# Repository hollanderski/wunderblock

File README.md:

# Wunderblock
webGL interface for "Wunderblock", art installation exhibited at PHITECO 2022

<br>

Created by Ninon Lizé Masclef and Syd Reynal, the installation Wunderblock proposes a reflection on telepresence and the ambivalence it carries through the oppositions presence-absence, virtual-embodied, simultaneity-latency. Wunderblock mediates the touch, through a tension between organic traces embedded in the material of a tactile sensor and digital traces reincarnated in the flesh of the virtual world.
As it breaks the simultaneity traditionally at work in the real-time human-machine interface, Wunderblock opens up power of the après-coup. From traces on the walls of Lascaux to the prophylaxis of the Metaverse, this work thus questions the multiplicity of modes of collective presence and forms of memories that materialize there.

The installation was exhibited during the seminar PHITECO (Philosophy Technology Cognition) 2022 at University of Technology of Compiègne whose theme was : "Technical mediation of presence". Read the <a href="http://ninonlm.com/hyperobjects/wunderblock/program.pdf">full program</a> of the seminar. 

<br>

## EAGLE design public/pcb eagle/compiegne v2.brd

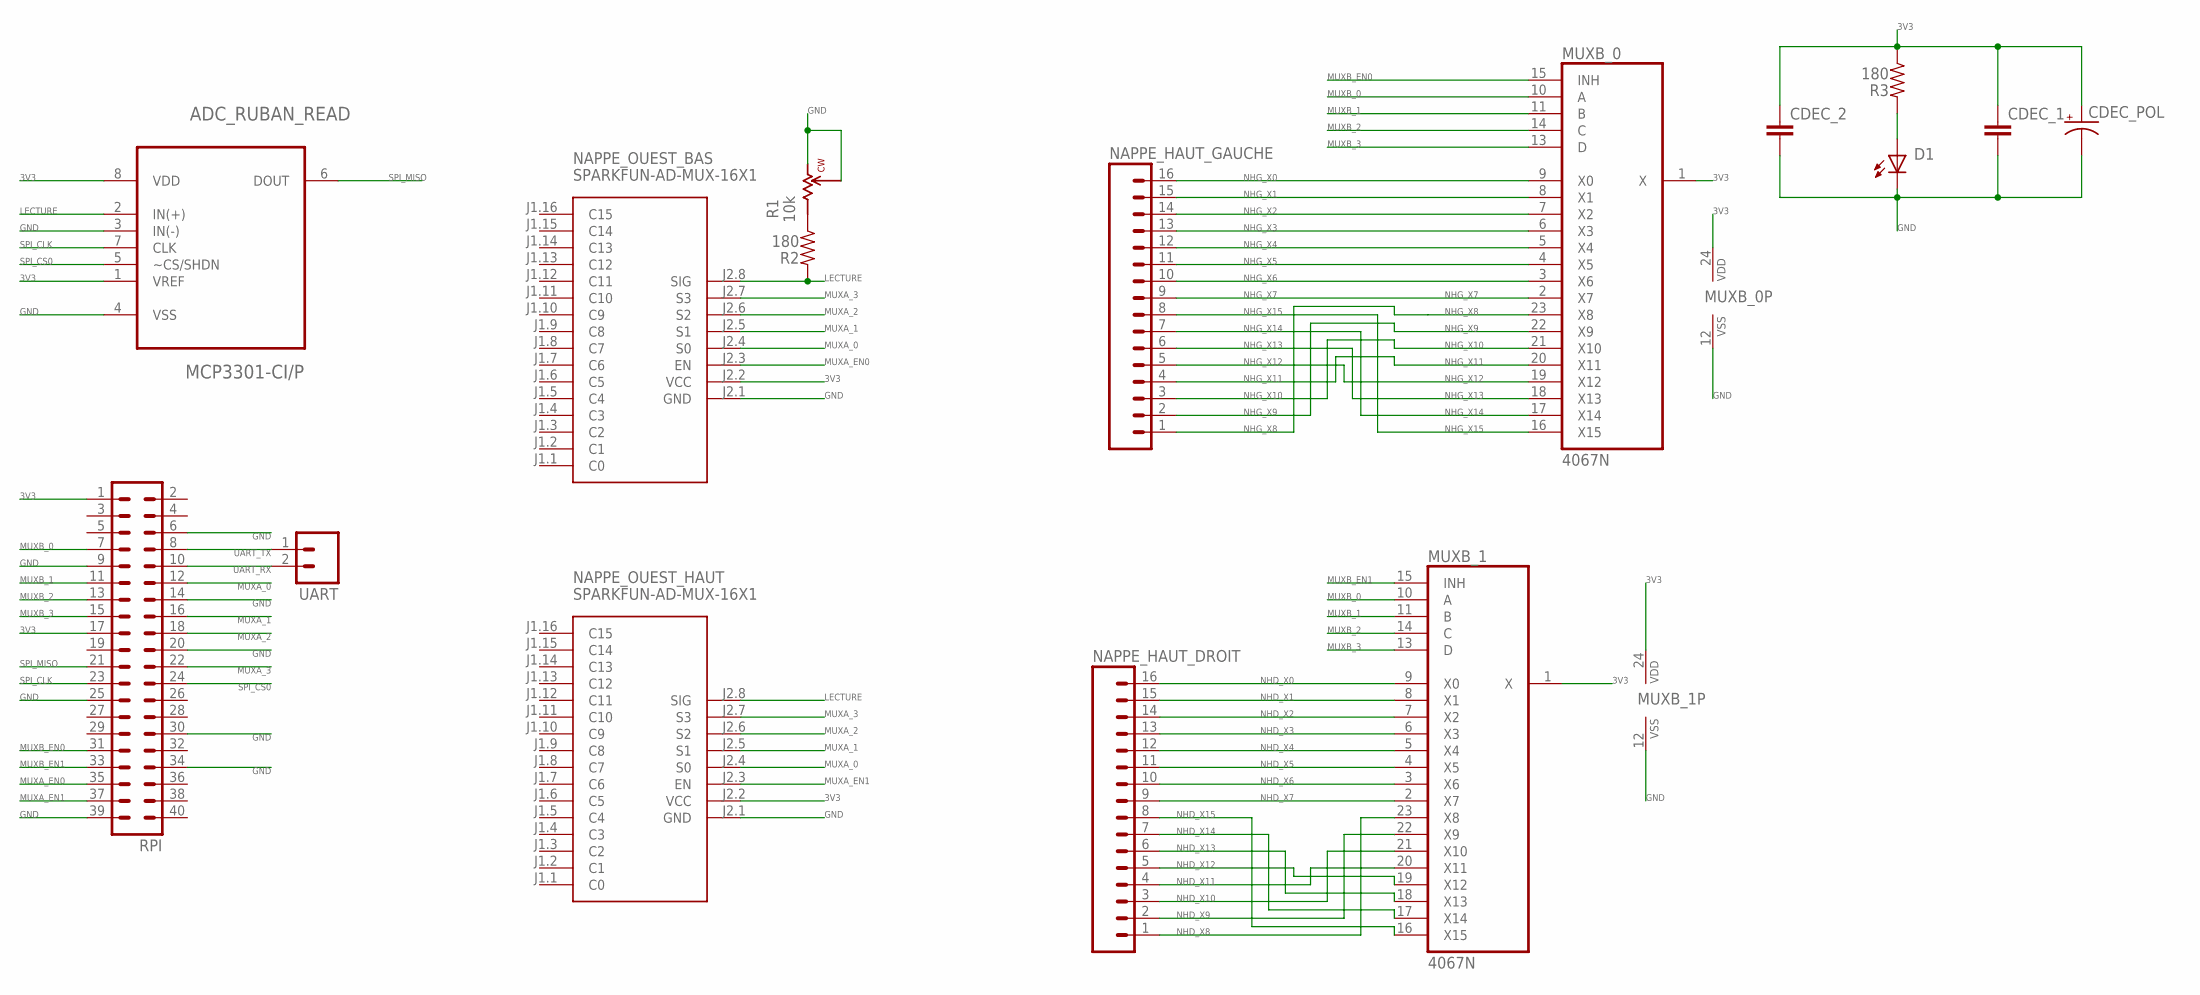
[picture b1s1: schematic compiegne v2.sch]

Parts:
ADC_RUBAN_READ: MCP3301-CI/P; DIP254P762X432-8
CDEC_1, CDEC_2: PASSIF-CAP-PTH; CAP-PTH
CDEC_POL: PASSIF-CAP_POL-TANTALUM-PTH; CAP_POL-TANTALUM-PTH
D1: LED-3MM; 3MM-LED
MUXB_0, MUXB_1: 4067N; DIL24-6
NAPPE_HAUT_DROIT: MA16; 16PA
NAPPE_HAUT_GAUCHE: MA16; 16PA
NAPPE_OUEST_BAS: SPARKFUN-AD-MUX-16X1
NAPPE_OUEST_HAUT: SPARKFUN-AD-MUX-16X1
R1: 10k; TRIMPOT_3266
R2, R3: 180; RESISTOR-PTH
RPI: MA20-2
UART: MA02; 02PA

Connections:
3V3: ADC_RUBAN_READ.1 (VREF), ADC_RUBAN_READ.8 (VDD), CDEC_1.P$1 (1), CDEC_2.P$1 (1), CDEC_POL.+, MUXB_0.1 (X), MUXB_0.24 (VDD), MUXB_1.1 (X), MUXB_1.24 (VDD), NAPPE_OUEST_BAS.J2.2 (VCC), NAPPE_OUEST_HAUT.J2.2 (VCC), R3.P$1 (1), RPI.1, RPI.17
GND: ADC_RUBAN_READ.3 (IN(-)), ADC_RUBAN_READ.4 (VSS), CDEC_1.P$2 (2), CDEC_2.P$2 (2), CDEC_POL.-, D1.C, MUXB_0.12 (VSS), MUXB_1.12 (VSS), NAPPE_OUEST_BAS.J2.1 (GND), NAPPE_OUEST_HAUT.J2.1 (GND), R1.2, R1.3, RPI.6, RPI.9, RPI.14, RPI.20, RPI.25, RPI.30, RPI.34, RPI.39
LECTURE: ADC_RUBAN_READ.2 (IN(+)), NAPPE_OUEST_BAS.J2.8 (SIG), NAPPE_OUEST_HAUT.J2.8 (SIG), R2.P$2 (2)
MUXA_0: NAPPE_OUEST_BAS.J2.4 (S0), NAPPE_OUEST_HAUT.J2.4 (S0), RPI.12
MUXA_1: NAPPE_OUEST_BAS.J2.5 (S1), NAPPE_OUEST_HAUT.J2.5 (S1), RPI.16
MUXA_2: NAPPE_OUEST_BAS.J2.6 (S2), NAPPE_OUEST_HAUT.J2.6 (S2), RPI.18
MUXA_3: NAPPE_OUEST_BAS.J2.7 (S3), NAPPE_OUEST_HAUT.J2.7 (S3), RPI.22
MUXA_EN0: NAPPE_OUEST_BAS.J2.3 (EN), RPI.35
MUXA_EN1: NAPPE_OUEST_HAUT.J2.3 (EN), RPI.37
MUXB_0: MUXB_0.10 (A), MUXB_1.10 (A), RPI.7
MUXB_1: MUXB_0.11 (B), MUXB_1.11 (B), RPI.11
MUXB_2: MUXB_0.14 (C), MUXB_1.14 (C), RPI.13
MUXB_3: MUXB_0.13 (D), MUXB_1.13 (D), RPI.15
MUXB_EN0: MUXB_0.15 (INH), RPI.31
MUXB_EN1: MUXB_1.15 (INH), RPI.33
unnamed: R1.1, R2.P$1 (1)
unnamed: D1.A, R3.P$2 (2)
NHD_X0: MUXB_1.9 (X0), NAPPE_HAUT_DROIT.16
NHD_X1: MUXB_1.8 (X1), NAPPE_HAUT_DROIT.15
NHD_X2: MUXB_1.7 (X2), NAPPE_HAUT_DROIT.14
NHD_X3: MUXB_1.6 (X3), NAPPE_HAUT_DROIT.13
NHD_X4: MUXB_1.5 (X4), NAPPE_HAUT_DROIT.12
NHD_X5: MUXB_1.4 (X5), NAPPE_HAUT_DROIT.11
NHD_X6: MUXB_1.3 (X6), NAPPE_HAUT_DROIT.10
NHD_X7: MUXB_1.2 (X7), NAPPE_HAUT_DROIT.9
NHD_X8: MUXB_1.23 (X8), NAPPE_HAUT_DROIT.1
NHD_X9: MUXB_1.22 (X9), NAPPE_HAUT_DROIT.2
NHD_X10: MUXB_1.21 (X10), NAPPE_HAUT_DROIT.3
NHD_X11: MUXB_1.20 (X11), NAPPE_HAUT_DROIT.4
NHD_X12: MUXB_1.19 (X12), NAPPE_HAUT_DROIT.5
NHD_X13: MUXB_1.18 (X13), NAPPE_HAUT_DROIT.6
NHD_X14: MUXB_1.17 (X14), NAPPE_HAUT_DROIT.7
NHD_X15: MUXB_1.16 (X15), NAPPE_HAUT_DROIT.8
NHG_X0: MUXB_0.9 (X0), NAPPE_HAUT_GAUCHE.16
NHG_X1: MUXB_0.8 (X1), NAPPE_HAUT_GAUCHE.15
NHG_X2: MUXB_0.7 (X2), NAPPE_HAUT_GAUCHE.14
NHG_X3: MUXB_0.6 (X3), NAPPE_HAUT_GAUCHE.13
NHG_X4: MUXB_0.5 (X4), NAPPE_HAUT_GAUCHE.12
NHG_X5: MUXB_0.4 (X5), NAPPE_HAUT_GAUCHE.11
NHG_X6: MUXB_0.3 (X6), NAPPE_HAUT_GAUCHE.10
NHG_X7: MUXB_0.2 (X7), NAPPE_HAUT_GAUCHE.9
NHG_X8: MUXB_0.23 (X8), NAPPE_HAUT_GAUCHE.1
NHG_X9: MUXB_0.22 (X9), NAPPE_HAUT_GAUCHE.2
NHG_X10: MUXB_0.21 (X10), NAPPE_HAUT_GAUCHE.3
NHG_X11: MUXB_0.20 (X11), NAPPE_HAUT_GAUCHE.4
NHG_X12: MUXB_0.19 (X12), NAPPE_HAUT_GAUCHE.5
NHG_X13: MUXB_0.18 (X13), NAPPE_HAUT_GAUCHE.6
NHG_X14: MUXB_0.17 (X14), NAPPE_HAUT_GAUCHE.7
NHG_X15: MUXB_0.16 (X15), NAPPE_HAUT_GAUCHE.8
SPI_CLK: ADC_RUBAN_READ.7 (CLK), RPI.23
SPI_CS0: ADC_RUBAN_READ.5 (~CS/SHDN), RPI.24
SPI_MISO: ADC_RUBAN_READ.6 (DOUT), RPI.21
UART_RX: RPI.10, UART.2
UART_TX: RPI.8, UART.1

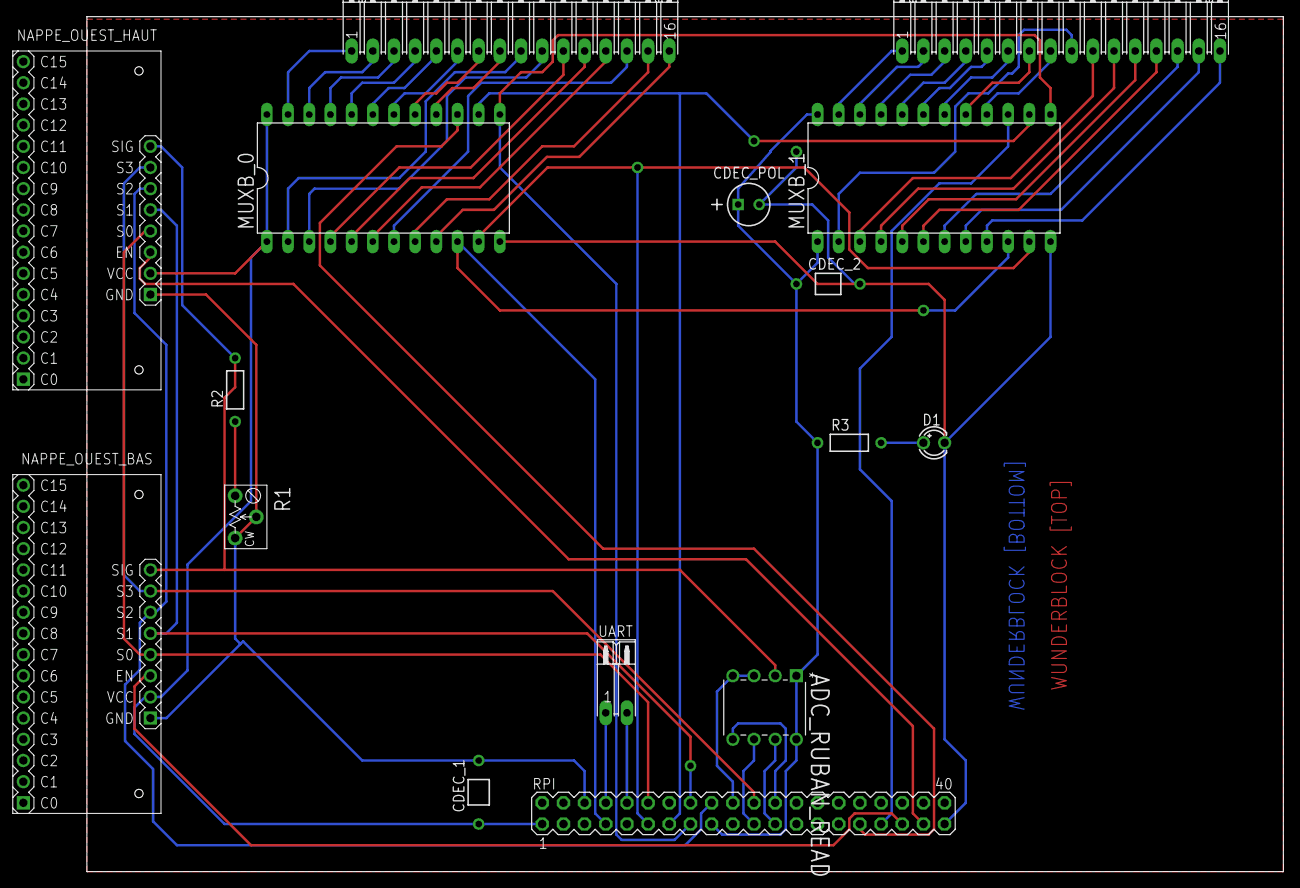
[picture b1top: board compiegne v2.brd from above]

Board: 2 copper layers, 143.5 x 102.5 mm, 16 parts (0 on the bottom side), 54 nets.

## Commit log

2022-01-04 basic example
2022-01-08 add mesh + skin texture
2022-01-10 unreal bloom shader
2022-01-10 archi
2022-01-17 utils raspberry
2022-01-17 local dependencies'
2022-01-18 rename
2022-01-18 post trace
2022-01-18 sendTrace
2022-01-23 Create .gitignore
    Ajout .gitignore pour updater proprement depuis un Mac : filtre .DS_Store et Icon.
2022-01-23 Update .gitignore
    Ajout filtre EAGLE pour ne pas uploader les backups : .b#? et s#?
2022-01-23 PCB pour piloter les bandes de cuivre avec une carte RPi 3 ou 4
2022-01-23 Code micropython pour ESP32 DevKit v4
    Code pour piloter les rubans de LED NeoPixel WS2812
2022-01-23 Code Python pour Raspberry Pi 3
    Scan de la matrice tactile (32 + 32 bandes de cuivre), conversion de l'image via OpenCV et envoie au serveur par requete post.
2022-10-14 fix bug PositionalAudio
2022-10-14 solve positional audio bug
2023-05-13 add file + data sample

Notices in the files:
parts and their libraries:
DIY-modules: Released under the Creative Commons Attribution 4.0 International License: http://creativecommons.org/licenses/by/4.0
